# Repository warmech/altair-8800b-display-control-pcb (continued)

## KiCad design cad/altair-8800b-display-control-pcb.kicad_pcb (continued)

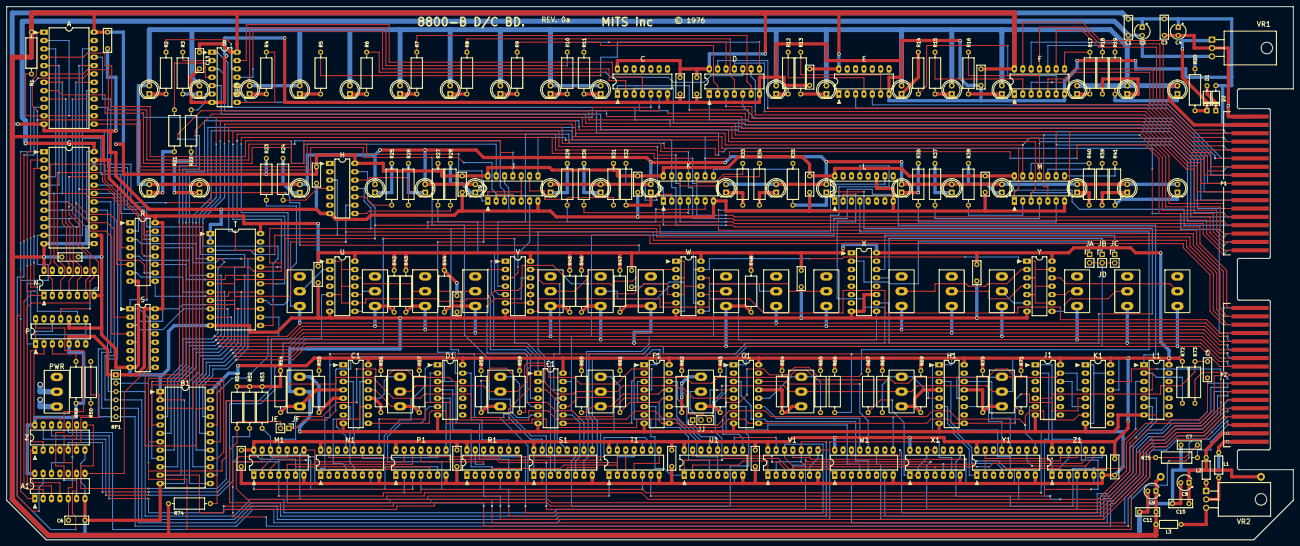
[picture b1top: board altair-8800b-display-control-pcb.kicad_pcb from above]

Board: 2 copper layers, 391.0 x 162.0 mm, 231 parts (1 on the bottom side), 300 nets.

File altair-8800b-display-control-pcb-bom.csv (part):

Source:,,,,,,,,,
Date:,9/16/2025 17:35,,,,,,,,
Tool:,Eeschema 7.0.11-rc3,,,,,,,,
Generator:,,,,,,,,,
Component Count:,232,,,,,,,,
,,,,,,,,,
Collated Components:,,,,,,,,,
,,,,,,,,,
Item,Qty,Reference(s),Value,LibPart,Footprint,Datasheet,DNP,Sim.Device,Sim.Pins
1,26,"C1, C3, C10, C11, C12, C13, C14, C15, C16, C17, C18, C19, C20, C21, C22, C23, C24, C25, C26, C27, C28, C29, C30, C31, C32, C33",0.1uF / 16V,Device:C,Capacitor_THT_Custom:C_Disc_D7.0mm_W2.3mm_P5.00mm,~,,,
2,4,"C2, C4, C8, C9",47uF / 16V,Device:C_Polarized_US,Capacitor_THT:CP_Radial_Tantal_D4.5mm_P2.50mm,~,,,
3,3,"C5, C6, C7",0.001uF,Device:C,Capacitor_THT_Custom:C_Disc_D7.0mm_W2.3mm_P5.00mm,~,,,
4,2,"D1, D2",1N914,Diode:1N914,Diode_THT:D_DO-35_SOD27_P7.62mm_Horizontal,http://www.vishay.com/docs/85622/1n914.pdf,,D,1=K 2=A
5,1,J1,JF_JE,Connector_Generic:Conn_01x02,Connector_PinHeader_2.54mm:PinHeader_1x02_P2.54mm_Vertical,~,,,
6,1,JP1,JA,Jumper:Jumper_2_Open,Connector_PinHeader_2.54mm:PinHeader_1x02_P2.54mm_Vertical,~,,,
7,1,JP2,JB,Jumper:Jumper_2_Open,Connector_PinHeader_2.54mm:PinHeader_1x02_P2.54mm_Vertical,~,,,
8,1,JP3,JC,Jumper:Jumper_2_Open,Connector_PinHeader_2.54mm:PinHeader_1x02_P2.54mm_Vertical,~,,,
9,1,JP4,G_H_J,Jumper:Jumper_3_Bridged12,Connector_PinHeader_2.54mm:PinHeader_1x03_P2.54mm_Vertical,~,,,
10,3,"L1, L2, L3",L,Device:L,Inductor_THT:L_Axial_L5.3mm_D2.2mm_P7.62mm_Horizontal_Vishay_IM-1,~,,,
11,36,"LED1, LED2, LED3, LED4, LED5, LED6, LED7, LED8, LED9, LED10, LED11, LED12, LED13, LED14, LED15, LED16, LED17, LED18, LED19, LED20, LED21, LED22, LED23, LED24, LED25, LED26, LED27, LED28, LED29, LED30, LED31, LED32, LED33, LED34, LED35, LED36",LED,Device:LED,LED_THT:LED_D5.0mm,~,,,
12,1,P1,D/C Card Edge,:Ribbon_Cable_Card_Edge_Connector_34_Pin_1,Connector_Custom:Altair_8800B_Display_Control_Card_Edge,,,,
13,1,P2,D/C Card Edge,Connector_Custom:Ribbon_Cable_Card_Edge_Connector_34_Pin,Connector_Custom:Altair_8800B_Display_Control_Card_Edge,,,,
14,34,"R1, R23, R27, R31, R42, R43, R44, R45, R46, R47, R48, R49, R51, R52, R53, R54, R55, R56, R57, R58, R59, R60, R61, R62, R63, R64, R65, R67, R68, R69, R70, R71, R72, R74",2.2K,Device:R_US,Resistor_THT:R_Axial_DIN0309_L9.0mm_D3.2mm_P12.70mm_Horizontal,~,,,
15,37,"R2, R3, R4, R5, R6, R7, R8, R9, R10, R11, R12, R13, R14, R15, R16, R17, R18, R19, R21, R22, R24, R25, R26, R28, R29, R30, R32, R33, R34, R35, R36, R37, R38, R39, R40, R41, R73",220,Device:R_US,Resistor_THT:R_Axial_DIN0309_L9.0mm_D3.2mm_P12.70mm_Horizontal,~,,,
16,1,R20,1K,Device:R_US,Resistor_THT:R_Axial_DIN0309_L9.0mm_D3.2mm_P12.70mm_Horizontal,~,,,
17,2,"R50, R75",100,Device:R_US,Resistor_THT:R_Axial_DIN0309_L9.0mm_D3.2mm_P12.70mm_Horizontal,~,,,
18,1,R66,470,Device:R_US,Resistor_THT:R_Axial_DIN0309_L9.0mm_D3.2mm_P12.70mm_Horizontal,~,,,
19,1,R76,5 Ohm / 4W,Device:R_US,Resistor_THT:R_Axial_DIN0516_L15.5mm_D5.0mm_P30.48mm_Horizontal,~,,,
20,1,RP1,4.7K,Device:R_Network05_Split,Resistor_THT:R_Array_SIP6,http://www.vishay.com/docs/31509/csc.pdf,,,
21,1,SW1,A0,Switch:SW_SPDT,Switch_Custom:Altair_Toggle_Switch,~,,,
22,1,SW2,A1,Switch:SW_SPDT,Switch_Custom:Altair_Toggle_Switch,~,,,
23,1,SW3,A2,Switch:SW_SPDT,Switch_Custom:Altair_Toggle_Switch,~,,,
24,1,SW4,A3,Switch:SW_SPDT,Switch_Custom:Altair_Toggle_Switch,~,,,
25,1,SW5,A4,Switch:SW_SPDT,Switch_Custom:Altair_Toggle_Switch,~,,,
26,1,SW6,A5,Switch:SW_SPDT,Switch_Custom:Altair_Toggle_Switch,~,,,
27,1,SW7,A6,Switch:SW_SPDT,Switch_Custom:Altair_Toggle_Switch,~,,,
28,1,SW8,A7,Switch:SW_SPDT,Switch_Custom:Altair_Toggle_Switch,~,,,
29,1,SW9,A8,Switch:SW_SPDT,Switch_Custom:Altair_Toggle_Switch,~,,,
30,1,SW10,A9,Switch:SW_SPDT,Switch_Custom:Altair_Toggle_Switch,~,,,
31,1,SW11,A10,Switch:SW_SPDT,Switch_Custom:Altair_Toggle_Switch,~,,,
32,1,SW12,A11,Switch:SW_SPDT,Switch_Custom:Altair_Toggle_Switch,~,,,
33,1,SW13,A12,Switch:SW_SPDT,Switch_Custom:Altair_Toggle_Switch,~,,,
34,2,"SW14, SW25",A13,Switch:SW_SPDT,Switch_Custom:Altair_Toggle_Switch,~,,,
35,1,SW15,A14,Switch:SW_SPDT,Switch_Custom:Altair_Toggle_Switch,~,,,
36,1,SW16,A15,Switch:SW_SPDT,Switch_Custom:Altair_Toggle_Switch,~,,,
37,1,SW17,STOP_RUN,Switch:SW_SPDT_MSM,Switch_Custom:Altair_Toggle_Switch_Momentary,~,,,
38,1,SW18,STEP_SLOW,Switch:SW_SPDT_MSM,Switch_Custom:Altair_Toggle_Switch_Momentary,~,,,
39,1,SW19,EXAMINE_NEXT,Switch:SW_SPDT_MSM,Switch_Custom:Altair_Toggle_Switch_Momentary,~,,,
40,1,SW20,DEPOSIT_NEXT,Switch:SW_SPDT_MSM,Switch_Custom:Altair_Toggle_Switch_Momentary,~,,,
41,1,SW21,ACC_DIS_DEP,Switch:SW_SPDT_MSM,Switch_Custom:Altair_Toggle_Switch_Momentary,~,,,
42,1,SW22,IN_OUT,Switch:SW_SPDT_MSM,Switch_Custom:Altair_Toggle_Switch_Momentary,~,,,
43,1,SW23,RESET_CLR,Switch:SW_SPDT_MSM,Switch_Custom:Altair_Toggle_Switch_Momentary,~,,,
44,1,SW24,PROT_UNPROT,Switch:SW_SPDT_MSM,Switch_Custom:Altair_Toggle_Switch_Momentary,~,,,
45,1,U1,8212 (A),Interface_Custom:8212,Package_DIP:DIP-24_W15.24mm_LongPads,,,,
46,1,U2,74LS07 (B),74xx:74LS07,Package_DIP:DIP-14_W7.62mm_LongPads,www.ti.com/lit/ds/symlink/sn74ls07.pdf,,,
47,1,U3,74LS04 (C),74xx:74LS04,Package_DIP:DIP-14_W7.62mm_LongPads,http://www.ti.com/lit/gpn/sn74LS04,,,
48,1,U4,74LS07 (D),74xx:74LS07,Package_DIP:DIP-14_W7.62mm_LongPads,www.ti.com/lit/ds/symlink/sn74ls07.pdf,,,
49,1,U5,74LS07 (E),74xx:74LS07,Package_DIP:DIP-14_W7.62mm_LongPads,www.ti.com/lit/ds/symlink/sn74ls07.pdf,,,
50,1,U6,74LS07 (F),74xx:74LS07,Package_DIP:DIP-14_W7.62mm_LongPads,www.ti.com/lit/ds/symlink/sn74ls07.pdf,,,
51,1,U8,74LS07 (H),74xx:74LS07,Package_DIP:DIP-14_W7.62mm_LongPads,www.ti.com/lit/ds/symlink/sn74ls07.pdf,,,
52,1,U9,74LS10 (J),74xx:74LS10,Package_DIP:DIP-14_W7.62mm_LongPads,http://www.ti.com/lit/gpn/sn74LS10,,,
53,1,U10,74LS07 (K),74xx:74LS07,Package_DIP:DIP-14_W7.62mm_LongPads,www.ti.com/lit/ds/symlink/sn74ls07.pdf,,,
54,1,U11,4040 (L),4xxx:4040,Package_DIP:DIP-16_W7.62mm_LongPads,http://www.intersil.com/content/dam/Intersil/documents/cd40/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,,,
55,1,U12,74LS07 (M),74xx:74LS07,Package_DIP:DIP-14_W7.62mm_LongPads,www.ti.com/lit/ds/symlink/sn74ls07.pdf,,,
56,1,U13,74LS30 (N),:74LS30_1,Package_DIP:DIP-14_W7.62mm_LongPads,http://www.ti.com/lit/gpn/sn74LS30,,,
57,1,U14,7493 (P),74xx_Custom:7493,Package_DIP:DIP-14_W7.62mm_LongPads,,,,
58,1,U15,74LS368 (R),74xx:74LS368,Package_DIP:DIP-16_W7.62mm_LongPads,http://www.ti.com/lit/gpn/sn74LS368,,,
59,1,U16,74LS368 (S),74xx:74LS368,Package_DIP:DIP-16_W7.62mm_LongPads,http://www.ti.com/lit/gpn/sn74LS368,,,
60,1,U17,8212 (T),Interface_Custom:8212,Package_DIP:DIP-24_W15.24mm_LongPads,,,,
61,1,U18,74LS05 (U),74xx:74LS05,Package_DIP:DIP-14_W7.62mm_LongPads,http://www.ti.com/lit/gpn/sn74LS05,,,
62,1,U19,74LS10 (V),74xx:74LS10,Package_DIP:DIP-14_W7.62mm_LongPads,http://www.ti.com/lit/gpn/sn74LS10,,,
63,1,U20,74LS05 (W),74xx:74LS05,Package_DIP:DIP-14_W7.62mm_LongPads,http://www.ti.com/lit/gpn/sn74LS05,,,
64,1,U21,4040 (X),4xxx:4040,Package_DIP:DIP-16_W7.62mm_LongPads,http://www.intersil.com/content/dam/Intersil/documents/cd40/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,,,
65,1,U22,74LS05 (Y),74xx:74LS05,Package_DIP:DIP-14_W7.62mm_LongPads,http://www.ti.com/lit/gpn/sn74LS05,,,
66,1,U23,74LS00 (Z),74xx:74LS00,Package_DIP:DIP-14_W7.62mm_LongPads,http://www.ti.com/lit/gpn/sn74ls00,,,
67,1,U24,74LS14 (A1),74xx:74LS14,Package_DIP:DIP-14_W7.62mm_LongPads,http://www.ti.com/lit/gpn/sn74LS14,,,
68,1,U25,8212 (B1),Interface_Custom:8212,Package_DIP:DIP-24_W15.24mm_LongPads,,,,
69,1,U26,74LS175 (C1),:74LS175_2,Package_DIP:DIP-16_W7.62mm_LongPads,http://www.ti.com/lit/gpn/sn74LS175,,,
70,1,U27,74LS10 (D1),74xx:74LS10,Package_DIP:DIP-14_W7.62mm_LongPads,http://www.ti.com/lit/gpn/sn74LS10,,,
71,1,U28,74LS04 (E1),74xx:74LS04,Package_DIP:DIP-14_W7.62mm_LongPads,http://www.ti.com/lit/gpn/sn74LS04,,,
72,1,U29,74LS175 (F1),:74LS175_3,Package_DIP:DIP-16_W7.62mm_LongPads,http://www.ti.com/lit/gpn/sn74LS175,,,
73,1,U30,74LS175 (G1),:74LS175_5,Package_DIP:DIP-16_W7.62mm_LongPads,http://www.ti.com/lit/gpn/sn74LS175,,,
74,1,U31,74LS175 (H1),:74LS175_4,Package_DIP:DIP-16_W7.62mm_LongPads,http://www.ti.com/lit/gpn/sn74LS175,,,
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
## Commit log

2025-10-20 Removed junk metadata files from project
